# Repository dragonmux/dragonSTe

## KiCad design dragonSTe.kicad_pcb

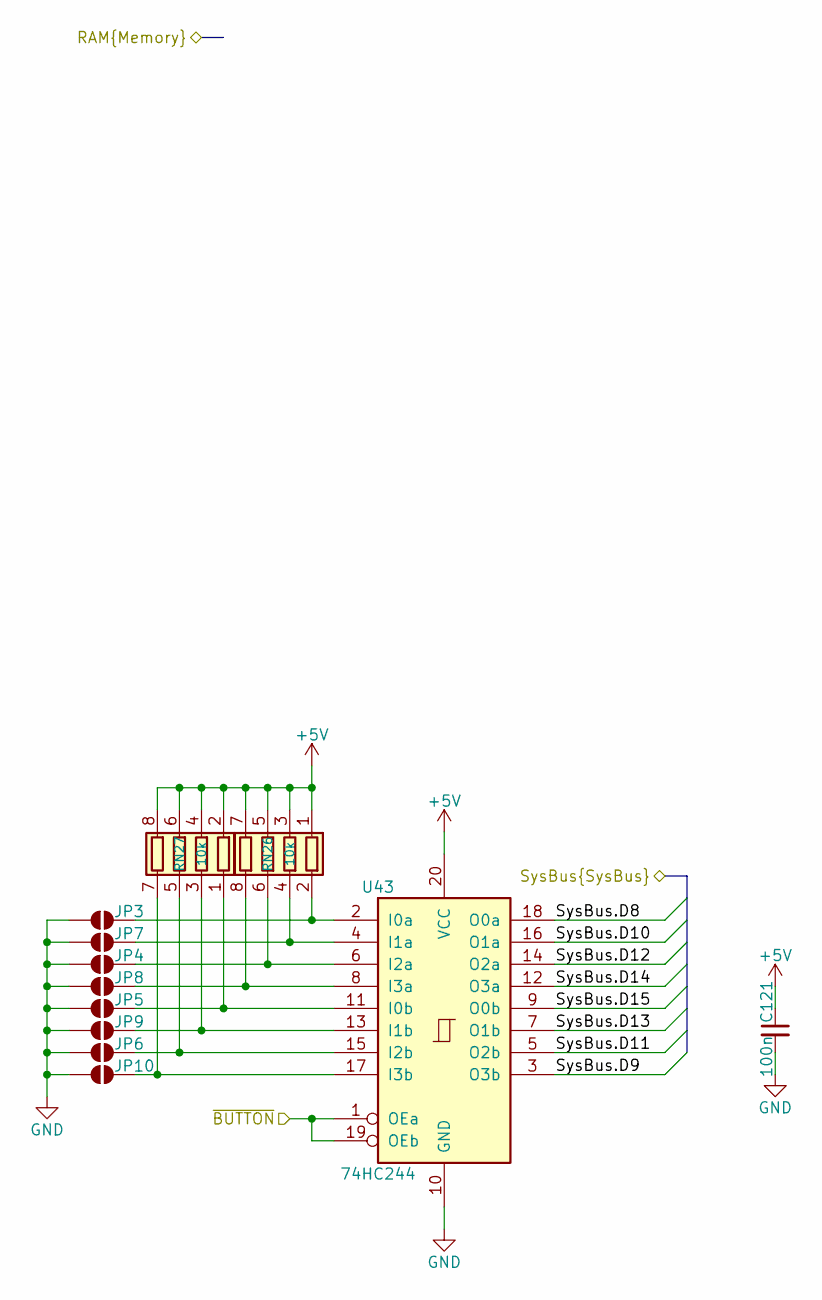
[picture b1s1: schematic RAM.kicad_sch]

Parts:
C121: 100n; C0603
JP3, JP4, JP5, JP6, JP7, JP8, JP9, JP10: SolderJumper_2_Open; SolderJumper-2_P1.3mm_Open_RoundedPad1.0x1.5mm
RN26, RN27: 10k; R0603_Array_Concave_4
U43: 74HC244; SO-20_12.8x7.5mm_P1.27mm; MPN 74HC244D,653

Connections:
+5V: C121.1, RN26.1 (R1.1), RN26.3 (R3.1), RN26.5 (R4.2), RN26.7 (R2.2), RN27.2 (R2.1), RN27.4 (R4.1), RN27.6 (R3.2), RN27.8 (R1.2), U43.20 (VCC); also elsewhere on the board
/CPU+ROMs/SysBus.D8: U43.18 (O0a); also elsewhere on the board
/CPU+ROMs/SysBus.D9: U43.3 (O3b); also elsewhere on the board
/CPU+ROMs/SysBus.D10: U43.16 (O1a); also elsewhere on the board
/CPU+ROMs/SysBus.D11: U43.5 (O2b); also elsewhere on the board
/CPU+ROMs/SysBus.D12: U43.14 (O2a); also elsewhere on the board
/CPU+ROMs/SysBus.D13: U43.7 (O1b); also elsewhere on the board
/CPU+ROMs/SysBus.D14: U43.12 (O3a); also elsewhere on the board
/CPU+ROMs/SysBus.D15: U43.9 (O0b); also elsewhere on the board
/DAC + Joysticks/~BUTTON: U43.1 (OEa), U43.19 (OEb); also elsewhere on the board
GND: C121.2, JP3.1 (A), JP4.1 (A), JP5.1 (A), JP6.1 (A), JP7.1 (A), JP8.1 (A), JP9.1 (A), JP10.1 (A), U43.10 (GND); also elsewhere on the board
unnamed: JP3.2 (B), RN26.2 (R2.1), U43.2 (I0a)
unnamed: JP4.2 (B), RN26.6 (R3.2), U43.6 (I2a)
unnamed: JP5.2 (B), RN27.1 (R1.1), U43.11 (I0b)
unnamed: JP6.2 (B), RN27.5 (R4.2), U43.15 (I2b)
unnamed: JP7.2 (B), RN26.4 (R4.1), U43.4 (I1a)
unnamed: JP8.2 (B), RN26.8 (R1.2), U43.8 (I3a)
unnamed: JP9.2 (B), RN27.3 (R3.1), U43.13 (I1b)
unnamed: JP10.2 (B), RN27.7 (R2.2), U43.17 (I3b)

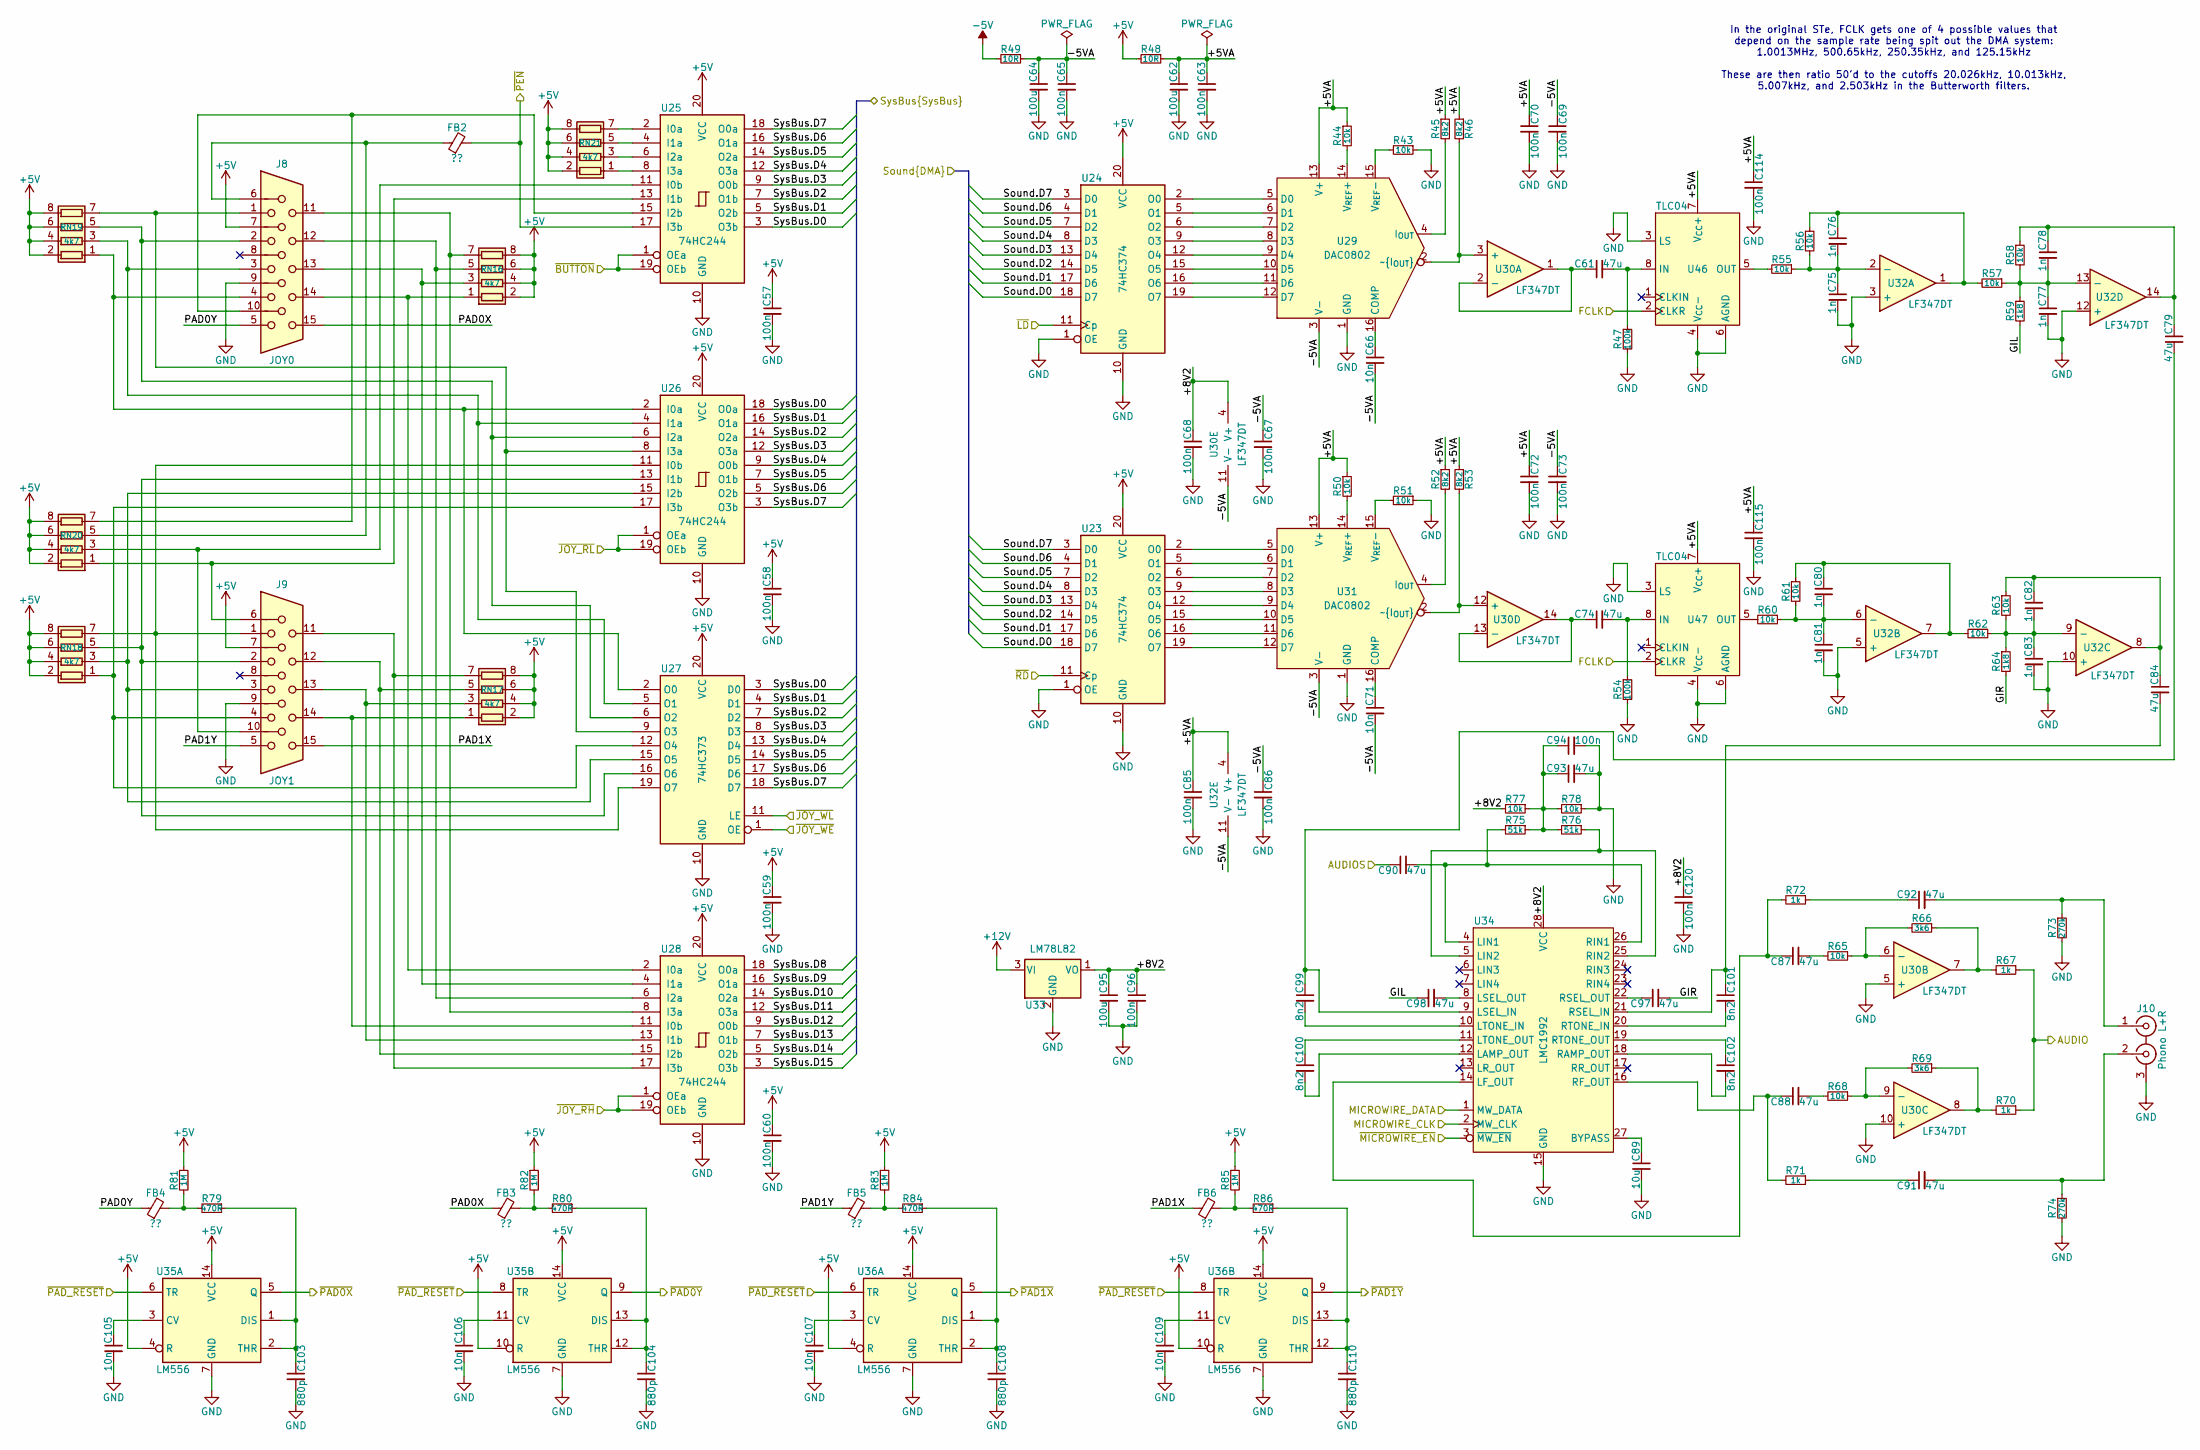
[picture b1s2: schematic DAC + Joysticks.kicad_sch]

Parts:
C57, C58, C59, C60, C63, C65, C67, C68, C69, C70, C72, C73, C85, C86, C94, C96, C114, C115, C120: 100n; C0603
C61, C74, C79, C84, C87, C88, C90, C91, C92, C93, C97, C98: 47u; C0603
C62, C64, C95: 100u; C0603
C66, C71, C105, C106, C107, C109: 10n; C0603
C75, C76, C77, C78, C80, C81, C82, C83: 1n; C0603
C89: 10u; C0603
C99, C100, C101, C102: 8n2; C0603
C103, C104, C108, C110: 880p; C0603
FB2, FB3, FB4, FB5, FB6: ??
J8: JOY0; DSUB-15-HD_Socket_Horizontal_P2.29x2.54mm_EdgePinOffset8.35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; MPN L77HDE15SD1CH4R
J9: JOY1; DSUB-15-HD_Socket_Horizontal_P2.29x2.54mm_EdgePinOffset8.35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; MPN L77HDE15SD1CH4R
J10: Phono L+R; PSG01550; MPN PSG01550
R43, R44, R50, R51, R55, R56, R57, R58, R60, R61, R62, R63, R65, R68, R77, R78: 10k; R0603
R45, R46, R52, R53: 8k2; R0603
R47, R54: 100k; R0603
R48, R49: 10R; R0603
R59, R64: 1k8; R0603
R66, R69: 3k6; R0603
R67, R70, R71, R72: 1k; R0603
R73, R74: 270k; R0603
R75, R76: 51k; R0603
R79, R80, R84, R86: 470R; R0603
R81, R82, R83, R85: 1M; R0603
RN16, RN17, RN18, RN19, RN20, RN21: 4k7; R0603_Array_Concave_4
U23, U24: 74HC374; SO-20_12.8x7.5mm_P1.27mm; MPN 74HC374D,653
U25, U26, U28: 74HC244; SO-20_12.8x7.5mm_P1.27mm; MPN 74HC244D,653
U27: 74HC373; SO-20_12.8x7.5mm_P1.27mm; MPN 74HC373D,653
U29, U31: DAC0802; SO-16_3.9x9.9mm_P1.27mm; MPN DAC0802
U30, U32: LF347DT; SO-14_3.9x8.65mm_P1.27mm; MPN LF347DT
U33: LM78L82; TO-92_Inline
U34: LMC1992; DIP-28_W15.24mm_Socket; MPN SPC15504
U35, U36: LM556
U46, U47: TLC04; SO-8_3.9x4.9mm_P1.27mm; MPN TLC04CD

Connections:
+5V: C57.1, C58.1, C59.1, C60.1, J8.7, J9.7, R48.2, R81.1, R82.1, R83.1, R85.1, RN16.2 (R2.1), RN16.4 (R4.1), RN16.6 (R3.2), RN16.8 (R1.2), RN17.2 (R2.1), RN17.4 (R4.1), RN17.6 (R3.2), RN17.8 (R1.2), RN18.2 (R2.1), RN18.4 (R4.1), RN18.6 (R3.2), RN18.8 (R1.2), RN19.2 (R2.1), RN19.4 (R4.1), RN19.6 (R3.2), RN19.8 (R1.2), RN20.2 (R2.1), RN20.4 (R4.1), RN20.6 (R3.2), RN20.8 (R1.2), RN21.2 (R2.1), RN21.4 (R4.1), RN21.6 (R3.2), RN21.8 (R1.2), U23.20 (VCC), U24.20 (VCC), U25.20 (VCC), U26.20 (VCC), U27.20 (VCC), U28.20 (VCC), U35.4 (R), U35.10 (R), U35.14 (VCC), U36.4 (R), U36.10 (R), U36.14 (VCC); also elsewhere on the board
+12V: U33.3 (VI); also elsewhere on the board
-5V: R49.2; also elsewhere on the board
/CPU+ROMs/SysBus.D0: U25.3 (O3b), U26.18 (O0a), U27.3 (D0); also elsewhere on the board
/CPU+ROMs/SysBus.D1: U25.5 (O2b), U26.16 (O1a), U27.4 (D1); also elsewhere on the board
/CPU+ROMs/SysBus.D2: U25.7 (O1b), U26.14 (O2a), U27.7 (D2); also elsewhere on the board
/CPU+ROMs/SysBus.D3: U25.9 (O0b), U26.12 (O3a), U27.8 (D3); also elsewhere on the board
/CPU+ROMs/SysBus.D4: U25.12 (O3a), U26.9 (O0b), U27.13 (D4); also elsewhere on the board
/CPU+ROMs/SysBus.D5: U25.14 (O2a), U26.7 (O1b), U27.14 (D5); also elsewhere on the board
/CPU+ROMs/SysBus.D6: U25.16 (O1a), U26.5 (O2b), U27.17 (D6); also elsewhere on the board
/CPU+ROMs/SysBus.D7: U25.18 (O0a), U26.3 (O3b), U27.18 (D7); also elsewhere on the board
/CPU+ROMs/SysBus.D8: U28.18 (O0a); also elsewhere on the board
/CPU+ROMs/SysBus.D9: U28.16 (O1a); also elsewhere on the board
/CPU+ROMs/SysBus.D10: U28.14 (O2a); also elsewhere on the board
/CPU+ROMs/SysBus.D11: U28.12 (O3a); also elsewhere on the board
/CPU+ROMs/SysBus.D12: U28.9 (O0b); also elsewhere on the board
/CPU+ROMs/SysBus.D13: U28.7 (O1b); also elsewhere on the board
/CPU+ROMs/SysBus.D14: U28.5 (O2b); also elsewhere on the board
/CPU+ROMs/SysBus.D15: U28.3 (O3b); also elsewhere on the board
/DAC + Joysticks/+5VA: C62.1, C63.1, C70.1, C72.1, C85.1, C114.1, C115.1, R44.1, R45.1, R46.1, R48.1, R50.1, R52.1, R53.1, U29.13 (V+), U31.13 (V+), U32.4 (V+), U46.7 (V_{CC}+), U47.7 (V_{CC}+)
/DAC + Joysticks/+8V2: C68.1, C95.1, C96.1, C120.1, R77.2, U30.4 (V+), U33.1 (VO), U34.28 (VCC)
/DAC + Joysticks/-5VA: C64.1, C65.1, C66.2, C67.1, C69.1, C71.2, C73.1, C86.1, R49.1, U29.3 (V-), U30.11 (V-), U31.3 (V-), U32.11 (V-)
/DAC + Joysticks/AUDIO: R67.1, R70.1
/DAC + Joysticks/AUDIOS: C90.1; also elsewhere on the board
/DAC + Joysticks/FCLK: U46.2 (CLKR), U47.2 (CLKR)
/DAC + Joysticks/GIL: C98.1, R59.2
/DAC + Joysticks/GIR: C97.2, R64.2
/DAC + Joysticks/MICROWIRE_CLK: U34.2 (MW_CLK); also elsewhere on the board
/DAC + Joysticks/MICROWIRE_DATA: U34.1 (MW_DATA); also elsewhere on the board
/DAC + Joysticks/PAD0X: FB3.1, J8.15
/DAC + Joysticks/PAD0Y: FB4.1, J8.5
/DAC + Joysticks/PAD1X: FB6.1, J9.15
/DAC + Joysticks/PAD1Y: FB5.1, J9.5
/DAC + Joysticks/Sound.D0: U23.18 (D7), U24.18 (D7); also elsewhere on the board
/DAC + Joysticks/Sound.D1: U23.17 (D6), U24.17 (D6); also elsewhere on the board
/DAC + Joysticks/Sound.D2: U23.14 (D5), U24.14 (D5); also elsewhere on the board
/DAC + Joysticks/Sound.D3: U23.13 (D4), U24.13 (D4); also elsewhere on the board
/DAC + Joysticks/Sound.D4: U23.8 (D3), U24.8 (D3); also elsewhere on the board
/DAC + Joysticks/Sound.D5: U23.7 (D2), U24.7 (D2); also elsewhere on the board
/DAC + Joysticks/Sound.D6: U23.4 (D1), U24.4 (D1); also elsewhere on the board
/DAC + Joysticks/Sound.D7: U23.3 (D0), U24.3 (D0); also elsewhere on the board
/DAC + Joysticks/~BUTTON: U25.1 (OEa), U25.19 (OEb); also elsewhere on the board
/DAC + Joysticks/~JOY_RH: U28.1 (OEa), U28.19 (OEb); also elsewhere on the board
/DAC + Joysticks/~JOY_RL: U26.1 (OEa), U26.19 (OEb); also elsewhere on the board
/DAC + Joysticks/~JOY_WE: U27.1 (OE); also elsewhere on the board
/DAC + Joysticks/~JOY_WL: U27.11 (LE); also elsewhere on the board
/DAC + Joysticks/~LD: U24.11 (Cp); also elsewhere on the board
/DAC + Joysticks/~MICROWIRE_EN: U34.3 (~MW_EN); also elsewhere on the board
/DAC + Joysticks/~PEN: FB2.2, U25.17 (I3b); also elsewhere on the board
/DAC + Joysticks/~RD: U23.11 (Cp); also elsewhere on the board
GND: C57.2, C58.2, C59.2, C60.2, C62.2, C63.2, C64.2, C65.2, C67.2, C68.2, C69.2, C70.2, C72.2, C73.2, C75.2, C77.2, C81.2, C83.2, C85.2, C86.2, C89.2, C93.2, C94.2, C95.2, C96.2, C103.2, C104.2, C105.2, C106.2, C107.2, C108.2, C109.2, C110.2, C114.2, C115.2, C120.2, J8.9, J9.9, J10.3 (EXT), R43.1, R47.2, R51.1, R54.2, R73.2, R74.2, R78.1, U23.1 (OE), U23.10 (GND), U24.1 (OE), U24.10 (GND), U25.10 (GND), U26.10 (GND), U27.10 (GND), U28.10 (GND), U29.1 (GND), U30.5 (+), U30.10 (+), U31.1 (GND), U32.3 (+), U32.5 (+), U32.10 (+), U32.12 (+), U33.2 (GND), U34.15 (GND), U35.7 (GND), U36.7 (GND), U46.3 (LS), U46.4 (V_{CC}-), U46.6 (AGND), U47.3 (LS), U47.4 (V_{CC}-), U47.6 (AGND); also elsewhere on the board
unnamed: C76.1, R56.1, R57.2, U32.1
unnamed: C78.1, C79.1, R58.1, U32.14
unnamed: C80.1, R61.1, R62.2, U32.7
unnamed: C82.1, C84.1, R63.1, U32.8
unnamed: C87.2, R65.2
unnamed: C88.2, R68.2
unnamed: C91.1, R71.1
unnamed: C92.1, R72.1
unnamed: C93.1, C94.1, R75.1, R76.2, R77.1, R78.2
unnamed: FB3.2, R80.2, R82.2
unnamed: FB4.2, R79.2, R81.2
unnamed: FB5.2, R83.2, R84.2
unnamed: FB6.2, R85.2, R86.2
unnamed: C92.2, J10.1 (IN1), R73.1
unnamed: C91.2, J10.2 (IN2), R74.1
unnamed: R66.1, R67.2, U30.7
unnamed: R69.1, R70.2, U30.8
unnamed: J8.14, RN16.1 (R1.1), U28.2 (I0a)
unnamed: J8.11, RN16.7 (R2.2), U28.8 (I3a)
unnamed: J8.13, RN16.3 (R3.1), U28.4 (I1a)
unnamed: J8.12, RN16.5 (R4.2), U28.6 (I2a)
unnamed: J9.14, RN17.1 (R1.1), U28.11 (I0b)
unnamed: J9.11, RN17.7 (R2.2), U28.17 (I3b)
unnamed: J9.13, RN17.3 (R3.1), U28.13 (I1b)
unnamed: J9.12, RN17.5 (R4.2), U28.15 (I2b)
unnamed: J9.4, RN18.1 (R1.1), U26.17 (I3b), U27.12 (O4)
unnamed: J9.1, RN18.7 (R2.2), U26.11 (I0b), U27.19 (O7)
unnamed: J9.3, RN18.3 (R3.1), U26.15 (I2b), U27.15 (O5)
unnamed: J9.2, RN18.5 (R4.2), U26.13 (I1b), U27.16 (O6)
unnamed: J8.4, RN19.1 (R1.1), U26.2 (I0a), U27.2 (O0)
unnamed: J8.1, RN19.7 (R2.2), U26.8 (I3a), U27.9 (O3)
unnamed: J8.3, RN19.3 (R3.1), U26.4 (I1a), U27.5 (O1)
unnamed: J8.2, RN19.5 (R4.2), U26.6 (I2a), U27.6 (O2)
unnamed: J9.6, RN20.1 (R1.1), U25.13 (I1b)
unnamed: J8.10, RN20.7 (R2.2), U25.15 (I2b)
unnamed: J9.10, RN20.3 (R3.1), U25.11 (I0b)
unnamed: FB2.1, J8.6, RN20.5 (R4.2)
unnamed: RN21.1 (R1.1), U25.8 (I3a)
unnamed: RN21.7 (R2.2), U25.2 (I0a)
unnamed: RN21.3 (R3.1), U25.6 (I2a)
unnamed: RN21.5 (R4.2), U25.4 (I1a)
unnamed: U23.2 (O0), U31.5 (D0)
unnamed: U23.5 (O1), U31.6 (D1)
unnamed: U23.6 (O2), U31.7 (D2)
unnamed: U23.9 (O3), U31.8 (D3)
unnamed: U23.12 (O4), U31.9 (D4)
unnamed: U23.15 (O5), U31.10 (D5)
unnamed: U23.16 (O6), U31.11 (D6)
unnamed: U23.19 (O7), U31.12 (D7)
unnamed: U24.2 (O0), U29.5 (D0)
unnamed: U24.5 (O1), U29.6 (D1)
unnamed: U24.6 (O2), U29.7 (D2)
unnamed: U24.9 (O3), U29.8 (D3)
unnamed: U24.12 (O4), U29.9 (D4)
unnamed: U24.15 (O5), U29.10 (D5)
unnamed: U24.16 (O6), U29.11 (D6)
unnamed: U24.19 (O7), U29.12 (D7)
unnamed: C66.1, U29.16 (COMP)
unnamed: R45.2, U29.4 (I_{OUT})
unnamed: R44.2, U29.14 (V_{REF}+)
unnamed: R43.2, U29.15 (V_{REF}-)
unnamed: R46.2, U29.2 (~I_{OUT}), U30.3 (+)
unnamed: C61.1, U30.1, U30.2 (-)
unnamed: R65.1, R66.2, U30.6 (-)
unnamed: R68.1, R69.2, U30.9 (-)
unnamed: R53.2, U30.12 (+), U31.2 (~I_{OUT})
unnamed: C74.1, U30.13 (-), U30.14
unnamed: C71.1, U31.16 (COMP)
unnamed: R52.2, U31.4 (I_{OUT})
unnamed: R50.2, U31.14 (V_{REF}+)
unnamed: R51.2, U31.15 (V_{REF}-)
unnamed: C75.1, C76.2, R55.1, R56.2, U32.2 (-)
unnamed: C80.2, C81.1, R60.1, R61.2, U32.6 (-)
unnamed: C82.2, C83.1, R62.1, R63.2, R64.1, U32.9 (-)
unnamed: C77.1, C78.2, R57.1, R58.2, R59.1, U32.13 (-)
unnamed: C89.1, U34.27 (BYPASS)
unnamed: C100.2, U34.12 (LAMP_OUT)
unnamed: C87.1, R72.2, U34.14 (LF_OUT)
unnamed: C90.2, R75.2, U34.4 (LIN1), U34.26 (RIN1)
unnamed: R76.1, U34.5 (LIN2), U34.25 (RIN2)
unnamed: C79.2, C99.1, U34.9 (LSEL_IN)
unnamed: C98.2, U34.8 (LSEL_OUT)
unnamed: C99.2, U34.10 (LTONE_IN)
unnamed: C100.1, U34.11 (LTONE_OUT)
unnamed: C102.2, U34.18 (RAMP_OUT)
unnamed: C88.1, R71.2, U34.16 (RF_OUT)
unnamed: C84.2, C101.1, U34.21 (RSEL_IN)
unnamed: C97.1, U34.22 (RSEL_OUT)
unnamed: C101.2, U34.20 (RTONE_IN)
unnamed: C102.1, U34.19 (RTONE_OUT)
unnamed: U35.6 (TR), U35.8 (TR), U36.6 (TR), U36.8 (TR)
unnamed: C105.1, U35.3 (CV)
unnamed: C103.1, R79.1, U35.1 (DIS), U35.2 (THR)
unnamed: C106.1, U35.11 (CV)
unnamed: C104.1, R80.1, U35.12 (THR), U35.13 (DIS)
unnamed: C107.1, U36.3 (CV)
unnamed: C108.1, R84.1, U36.1 (DIS), U36.2 (THR)
unnamed: C109.1, U36.11 (CV)
unnamed: C110.1, R86.1, U36.12 (THR), U36.13 (DIS)
unnamed: C61.2, R47.1, U46.8 (IN)
unnamed: R55.2, U46.5 (OUT)
unnamed: C74.2, R54.1, U47.8 (IN)
unnamed: R60.2, U47.5 (OUT)

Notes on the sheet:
In the original STe, FCLK gets one of 4 possible values that depend on the sample rate being spit out the DMA system: 1.0013MHz, 500.65kHz, 250.35kHz, and 125.15kHz These are then ratio 50'd to the cutoffs 20.026kHz, 10.013kHz, 5.007kHz, and 2.503kHz in the Butterworth filters.

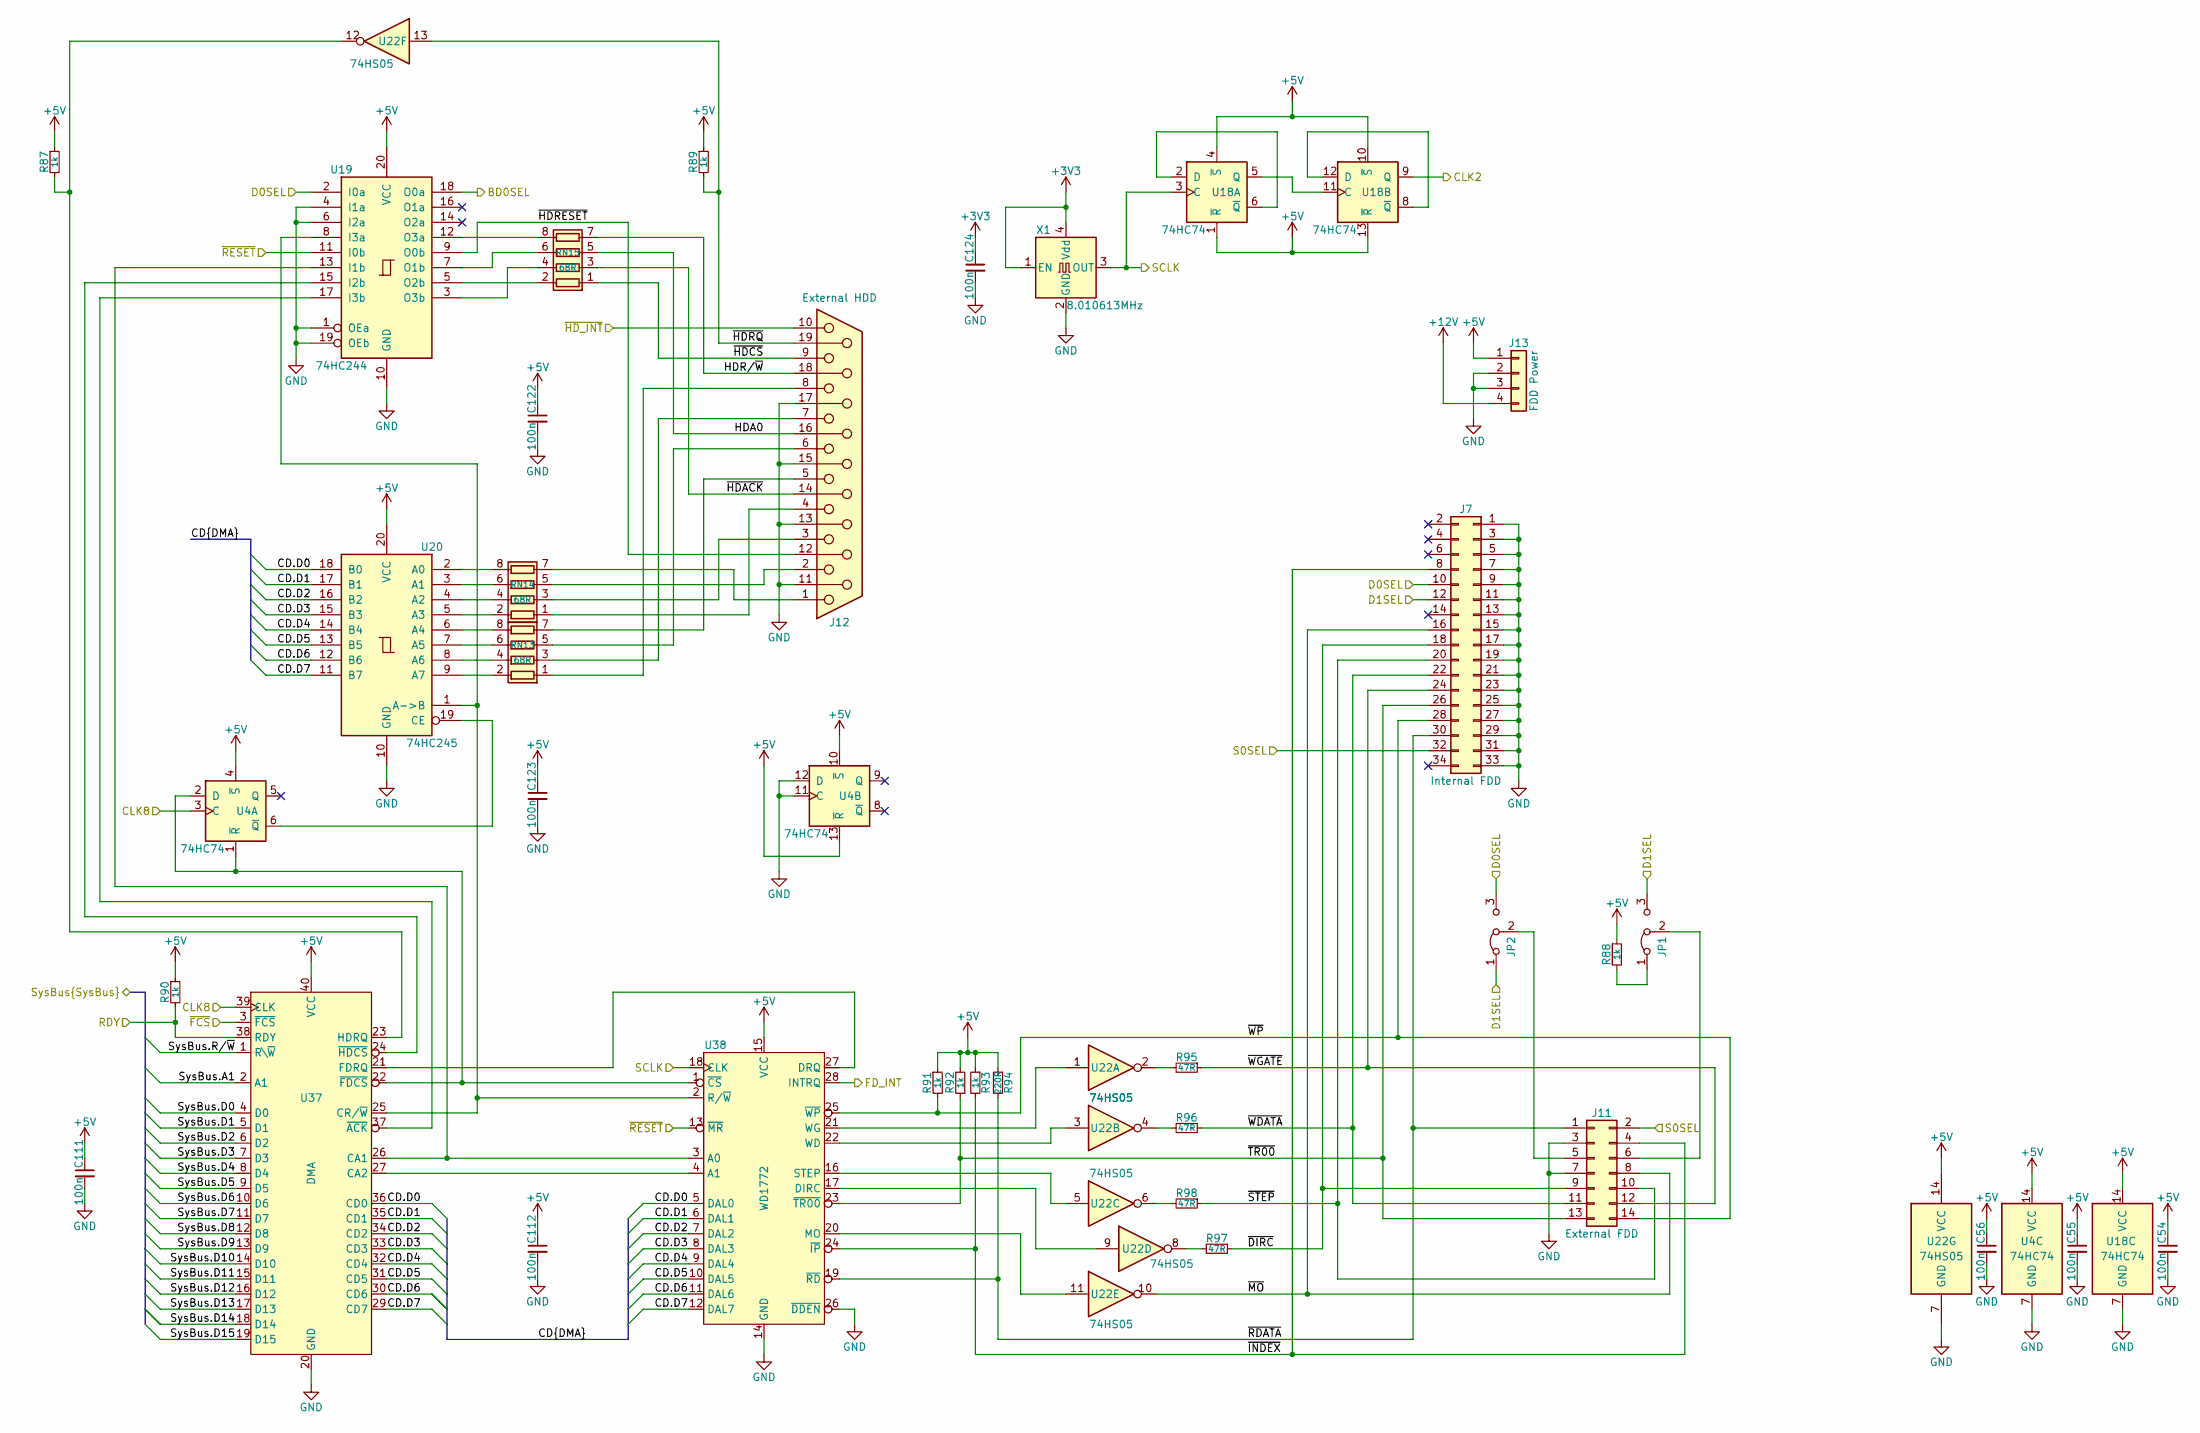
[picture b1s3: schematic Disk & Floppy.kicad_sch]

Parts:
C54, C55, C56, C111, C112, C122, C123, C124: 100n; C0603
J7: Internal FDD; PinHeader_2x17_P2.54mm_Vertical
J11: External FDD; PinHeader_2x07_P2.54mm_Horizontal
J12: External HDD
J13: FDD Power; PinHeader_1x04_P2.54mm_Vertical
JP1, JP2: Jumper_3_Bridged12; SolderJumper-3_P1.3mm_Bridged12_RoundedPad1.0x1.5mm_NumberL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
R87, R88, R89, R90, R91, R92, R93: 1k; R0603
R94: 220R; R0603
R95, R96, R97, R98: 47R; R0603
RN13, RN14, RN15: 68R; R0603_Array_Concave_4
U4, U18: 74HC74; SO-14_3.9x8.65mm_P1.27mm; MPN 74HC74D,653
U19: 74HC244; SO-20_12.8x7.5mm_P1.27mm; MPN 74HC244D,653
U20: 74HC245; SO-20_12.8x7.5mm_P1.27mm; MPN 74HC245D,653
U22: 74HS05; SO-14_3.9x8.65mm_P1.27mm; MPN SN74HC05DR
U37: DMA; DIP-40_W15.24mm_Socket; MPN SPC15505
U38: WD1772; DIP-28_W15.24mm_Socket; MPN SPC15504
X1: 8.010613MHz; SMD3225; MPN DSC8004CI2

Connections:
+3V3: C124.1, X1.1 (EN), X1.4 (Vdd); also elsewhere on the board
+5V: C54.1, C55.1, C56.1, C111.1, C112.1, C122.1, C123.1, J13.1, R87.1, R88.1, R89.1, R90.1, R91.1, R92.1, R93.1, R94.1, U4.4 (~S), U4.10 (~S), U4.13 (~R), U4.14 (VCC), U18.1 (~R), U18.4 (~S), U18.10 (~S), U18.13 (~R), U18.14 (VCC), U19.20 (VCC), U20.20 (VCC), U22.14 (VCC), U37.40 (VCC), U38.15 (VCC); also elsewhere on the board
+12V: J13.4; also elsewhere on the board
/CPU+ROMs/CLK8: U4.3 (C), U37.39 (CLK); also elsewhere on the board
/CPU+ROMs/SysBus.A1: U37.2 (A1); also elsewhere on the board
/CPU+ROMs/SysBus.D0: U37.4 (D0); also elsewhere on the board
/CPU+ROMs/SysBus.D1: U37.5 (D1); also elsewhere on the board
/CPU+ROMs/SysBus.D2: U37.6 (D2); also elsewhere on the board
/CPU+ROMs/SysBus.D3: U37.7 (D3); also elsewhere on the board
/CPU+ROMs/SysBus.D4: U37.8 (D4); also elsewhere on the board
/CPU+ROMs/SysBus.D5: U37.9 (D5); also elsewhere on the board
/CPU+ROMs/SysBus.D6: U37.10 (D6); also elsewhere on the board
/CPU+ROMs/SysBus.D7: U37.11 (D7); also elsewhere on the board
/CPU+ROMs/SysBus.D8: U37.12 (D8); also elsewhere on the board
/CPU+ROMs/SysBus.D9: U37.13 (D9); also elsewhere on the board
/CPU+ROMs/SysBus.D10: U37.14 (D10); also elsewhere on the board
/CPU+ROMs/SysBus.D11: U37.15 (D11); also elsewhere on the board
/CPU+ROMs/SysBus.D12: U37.16 (D12); also elsewhere on the board
/CPU+ROMs/SysBus.D13: U37.17 (D13); also elsewhere on the board
/CPU+ROMs/SysBus.D14: U37.18 (D14); also elsewhere on the board
/CPU+ROMs/SysBus.D15: U37.19 (D15); also elsewhere on the board
/CPU+ROMs/SysBus.R/~W: U37.1 (R\~W); also elsewhere on the board
/CPU+ROMs/~RESET: U19.11 (I0b), U38.13 (~MR); also elsewhere on the board
/Disk & Floppy/BD0SEL: U19.18 (O0a); also elsewhere on the board
/Disk & Floppy/CD.D0: U20.18 (B0), U37.36 (CD0), U38.5 (DAL0)
/Disk & Floppy/CD.D1: U20.17 (B1), U37.35 (CD1), U38.6 (DAL1)
/Disk & Floppy/CD.D2: U20.16 (B2), U37.34 (CD2), U38.7 (DAL2)
/Disk & Floppy/CD.D3: U20.15 (B3), U37.33 (CD3), U38.8 (DAL3)
/Disk & Floppy/CD.D4: U20.14 (B4), U37.32 (CD4), U38.9 (DAL4)
/Disk & Floppy/CD.D5: U20.13 (B5), U37.31 (CD5), U38.10 (DAL5)
/Disk & Floppy/CD.D6: U20.12 (B6), U37.30 (CD6), U38.11 (DAL6)
/Disk & Floppy/CD.D7: U20.11 (B7), U37.29 (CD7), U38.12 (DAL7)
/Disk & Floppy/CLK2: U18.9 (Q); also elsewhere on the board
/Disk & Floppy/D0SEL: J7.10, JP2.3 (B), U19.2 (I0a); also elsewhere on the board
/Disk & Floppy/D1SEL: J7.12, JP1.3 (B), JP2.1 (A); also elsewhere on the board
/Disk & Floppy/FD_INT: U38.28 (INTRQ); also elsewhere on the board
/Disk & Floppy/HDA0: J12.16, RN15.5 (R4.2)
/Disk & Floppy/HDR/~W: J12.18, RN15.7 (R2.2)
/Disk & Floppy/RDY: R90.2, U37.38 (RDY); also elsewhere on the board
/Disk & Floppy/S0SEL: J7.32, J11.2; also elsewhere on the board
/Disk & Floppy/SCLK: U18.3 (C), U38.18 (CLK), X1.3 (OUT); also elsewhere on the board
/Disk & Floppy/~DIRC: J7.18, J11.9, R97.1
/Disk & Floppy/~FCS: U37.3 (~FCS); also elsewhere on the board
/Disk & Floppy/~HDACK: J12.14, RN15.3 (R3.1)
/Disk & Floppy/~HDCS: J12.9, RN15.1 (R1.1)
/Disk & Floppy/~HDRESET: J12.12, U19.9 (O0b)
/Disk & Floppy/~HDRQ: J12.19, R89.2, U22.13
/Disk & Floppy/~INDEX: J7.8, J11.4, R93.2, U38.24 (~IP)
/Disk & Floppy/~MO: J7.16, J11.8, U22.10
/Disk & Floppy/~RDATA: J7.30, J11.1, R94.2, U38.19 (~RD)
/Disk & Floppy/~STEP: J7.20, J11.10, R98.1
/Disk & Floppy/~TR00: J7.26, J11.13, R92.2, U38.23 (~TR00)
/Disk & Floppy/~WDATA: J7.22, J11.11, R96.1
/Disk & Floppy/~WGATE: J7.24, J11.12, R95.1
/Disk & Floppy/~WP: J7.28, J11.14, R91.2, U38.25 (~WP)
GND: C54.2, C55.2, C56.2, C111.2, C112.2, C122.2, C123.2, C124.2, J7.1, J7.3, J7.5, J7.7, J7.9, J7.11, J7.13, J7.15, J7.17, J7.19, J7.21, J7.23, J7.25, J7.27, J7.29, J7.31, J7.33, J11.3, J11.7, J12.11, J12.13, J12.15, J12.17, J13.2, J13.3, U4.7 (GND), U4.11 (C), U4.12 (D), U18.7 (GND), U19.1 (OEa), U19.4 (I1a), U19.6 (I2a), U19.10 (GND), U19.19 (OEb), U20.10 (GND), U22.7 (GND), U37.20 (GND), U37.28 (GND), U38.14 (GND), U38.26 (~DDEN), X1.2 (GND); also elsewhere on the board
unnamed: J11.5, JP2.2 (C)
unnamed: J11.6, JP1.2 (C)
unnamed: JP1.1 (A), R88.2
unnamed: R95.2, U22.2
unnamed: R96.2, U22.4
unnamed: R97.2, U22.8
unnamed: R98.2, U22.6
unnamed: J12.8, RN13.1 (R1.1)
unnamed: RN13.8 (R1.2), U20.6 (A4)
unnamed: RN13.2 (R2.1), U20.9 (A7)
unnamed: J12.5, RN13.7 (R2.2)
unnamed: J12.7, RN13.3 (R3.1)
unnamed: RN13.6 (R3.2), U20.7 (A5)
unnamed: RN13.4 (R4.1), U20.8 (A6)
unnamed: J12.6, RN13.5 (R4.2)
unnamed: J12.4, RN14.1 (R1.1)
unnamed: RN14.8 (R1.2), U20.2 (A0)
unnamed: RN14.2 (R2.1), U20.5 (A3)
unnamed: J12.1, RN14.7 (R2.2)
unnamed: J12.3, RN14.3 (R3.1)
unnamed: RN14.6 (R3.2), U20.3 (A1)
unnamed: RN14.4 (R4.1), U20.4 (A2)
unnamed: J12.2, RN14.5 (R4.2)
unnamed: RN15.8 (R1.2), U19.12 (O3a)
unnamed: RN15.2 (R2.1), U19.5 (O2b)
unnamed: RN15.6 (R3.2), U19.7 (O1b)
unnamed: RN15.4 (R4.1), U19.3 (O3b)
unnamed: U18.2 (D), U18.6 (~Q)
unnamed: U18.5 (Q), U18.11 (C)
unnamed: U18.8 (~Q), U18.12 (D)
unnamed: U19.13 (I1b), U37.26 (CA1), U38.3 (A0)
unnamed: U19.15 (I2b), U37.24 (~HDCS)
unnamed: U19.8 (I3a), U20.1 (A->B), U37.25 (CR/~W), U38.2 (R/~W)
unnamed: U19.17 (I3b), U37.37 (~ACK)
unnamed: U4.6 (~Q), U20.19 (CE)
unnamed: U37.27 (CA2), U38.4 (A1)
unnamed: U37.21 (FDRQ), U38.27 (DRQ)
unnamed: R87.2, U22.12, U37.23 (HDRQ)
unnamed: U4.1 (~R), U4.2 (D), U37.22 (~FDCS), U38.1 (~CS)
unnamed: U22.9, U38.17 (DIRC)
unnamed: U22.11, U38.20 (MO)
unnamed: U22.5, U38.16 (STEP)
unnamed: U22.3, U38.22 (WD)
unnamed: U22.1, U38.21 (WG)
